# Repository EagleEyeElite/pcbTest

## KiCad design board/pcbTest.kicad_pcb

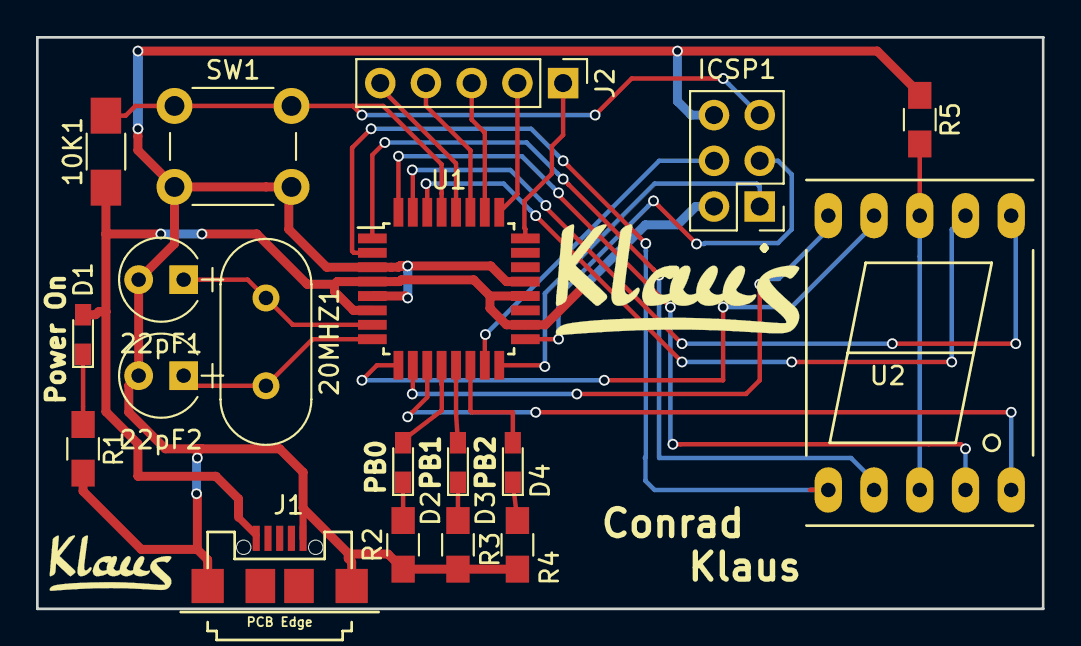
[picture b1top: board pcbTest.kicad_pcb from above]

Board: 2 copper layers, 55.9 x 31.8 mm, 19 parts (0 on the bottom side), 29 nets.

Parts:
10K1: R; R_1206_HandSoldering
20MHZ1: Crystal; Crystal_HC49-4H_Vertical
22pF1, 22pF2: CP; CP_Radial_Tantal_D4.5mm_P2.50mm
D1, D2, D3, D4: LED; LED_0603_HandSoldering
ICSP1: Conn_02x03_Odd_Even; Pin_Header_Straight_2x03_Pitch2.54mm
J1: USB_OTG; USB_Micro_Conn_Reichelt
J2: Conn_01x05_Female; Socket_Strip_Straight_1x05_Pitch2.54mm
R1, R2, R3, R4, R5: 220; R_0805_HandSoldering
SW1: SW_Push; SW_PUSH_6mm
U1: ATMEGA328P-AU; TQFP-32_7x7mm_Pitch0.8mm
U2: 7SEGMENT_CA; 7SegmentLED_LTS6760_LTS6780

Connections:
+5V: 10K1.1, D1.2, ICSP1.2, J1.1, U1.4, U1.6, U1.18, U1.20
GND: 22pF1.2, 22pF2.2, ICSP1.6, J1.5, J1.6, R1.2, R2.1, R3.1, R4.1, R5.1, SW1.2, U1.3, U1.5, U1.21
unnamed: 10K1.2, ICSP1.5, SW1.1, U1.29
unnamed: 20MHZ1.1, 22pF1.1, U1.7
unnamed: 20MHZ1.2, 22pF2.1, U1.8
unnamed: D1.1, R1.1
unnamed: D2.1, R2.2
unnamed: D2.2, U1.12
unnamed: D3.1, R3.2
unnamed: D3.2, U1.13
unnamed: D4.1, R4.2
unnamed: D4.2, U1.14
unnamed: ICSP1.1, U1.16
unnamed: ICSP1.3, U1.17
unnamed: ICSP1.4, U1.15
unnamed: J2.1, U1.24
unnamed: J2.2, U1.25
unnamed: J2.3, U1.26
unnamed: J2.4, U1.27
unnamed: J2.5, U1.28
unnamed: R5.2, U2.3, U2.8
unnamed: U1.1, U2.2
unnamed: U1.2, U2.1
unnamed: U1.9, U2.9
unnamed: U1.10, U2.10
unnamed: U1.11, U2.5
unnamed: U1.30, U2.7
unnamed: U1.31, U2.6
unnamed: U1.32, U2.4

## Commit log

2020-04-17 add Files
